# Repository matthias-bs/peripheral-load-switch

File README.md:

# peripheral-load-switch

Compact SMD peripheral load switch based on the Vishay SiP32431, designed for enabling/disabling power to microcontroller peripherals.

## Description

A minimal, all-SMD load switch board for switching a peripheral's supply voltage under microcontroller control. The design uses the Vishay **SiP32431DR3** high-side switch in a SC-70-6 (SOT-363) package. Board-edge castellated contacts (J2, half-hole, DNP) allow direct PCB-to-PCB soldering or surface mounting. An optional 5-pin 2.54 mm pitch pin header (J1) provides access for prototyping with breadboards or Dupont wires.

## SiP32431 Key Specifications

Datasheet: [SiP32431 (Vishay, PDF)](https://www.vishay.com/docs/66597/sip32431.pdf)

| Parameter               | Value                              |
|-------------------------|------------------------------------|
| Operating voltage       | 1.5 V – 5.5 V                      |
| Max continuous current  | 1.2 A                              |
| R<sub>DS(on)</sub>      | 147 mΩ                             |
| Package                 | SC-70-6 (JEITA) / SOT-363 (JEDEC)  |
| Enable logic            | Active-high                        |
| Switch type             | High-side                          |
| Leakage current         | 10 pA (ultra-low)                  |
| Special features        | Reverse current blocking, soft-start, ultra-low quiescent current |

## PCB & Schematic Features

- All-SMD design; 0805 passives are (more or less) hand-solderable, SC-70-6 IC requires reflow soldering
- 1 MΩ pull-down on EN pin ensures switch-off when enable is floating
- 1 µF input and 100 nF output decoupling capacitors
- 5-pin 2.54 mm pitch half-hole edge connector (J2, DNP) — castellated board-edge contacts for PCB-to-PCB or surface mounting
- 5-pin 2.54 mm pitch pin header (J1, optional) — for PCB-to-PCB stacking or prototyping with breadboards or Dupont wires
- DRC-clean design (0 violations, 0 unconnected pads)
- KiCad 9 source files with custom `Edge_HalfHole_5Pin_2.54mm` footprint included

## Schematic Preview

*Click image to open interactive schematic viewer (KiCanvas)*

## Interactive 3D PCB View

*Click image to open the interactive 3D model viewer (rotate/zoom/pan) — or use [KiCanvas](https://kicanvas.org/?github=https%3A%2F%2Fgithub.com%2Fmatthias-bs%2Fperipheral-load-switch%2Fblob%2Fmain%2Fload_switch.kicad_pcb) for a full PCB layer inspector*

> **How it was generated:** The 3D model ([`docs/load_switch.glb`](docs/load_switch.glb)) was exported from KiCad 9 using `kicad-cli pcb export glb` with tracks, pads, zones, silkscreen and soldermask included. The viewer ([`docs/index.html`](docs/index.html)) is a custom [Three.js](https://threejs.org/) page served via GitHub Pages.

## Bill of Materials

| Ref      | Value       | Footprint        | Description                        | LCSC Part # |
|----------|-------------|------------------|------------------------------------|-------------|
| U1       | SiP32431DR3 | SC-70-6 (SOT-363)| High-side load switch              | [C141606](https://www.lcsc.com/product-detail/C141606.html) |
| R1       | 1 MΩ        | 0805             | Pull-down on EN pin                | [C17514](https://www.lcsc.com/product-detail/C17514.html)  |
| C_IN1    | 1 µF        | 0805             | Input decoupling capacitor         | [C1712](https://www.lcsc.com/product-detail/C1712.html)   |
| C_OUT1   | 100 nF      | 0805             | Output decoupling capacitor        | [C126469](https://www.lcsc.com/product-detail/C126469.html) |
| J1       | —           | PinSocket 1×5 2.54 mm     | Optional pin header | — |
| J2       | —           | Half-hole 5-pin 2.54 mm (DNP¹) | Edge connector | — |

> ¹ DNP = Do Not Populate — the half-hole edge connector (J2) is a PCB manufacturing feature: the through-holes are routed in half at the board edge to form castellated contacts. No separate component is soldered.
>
> LCSC Part # are ordering references for [lcsc.com](https://lcsc.com).

## Connector Pinout (J2 — half-hole edge connector)

| Pin | Signal | Description          |
|-----|--------|----------------------|
| 1   | GND    | Ground               |
| 2   | GND    | Ground               |
| 3   | EN     | Enable (active-high) |
| 4   | OUT    | Switched output      |
| 5   | IN     | Supply voltage input |

## Production Files

Ready-to-order Gerber files (standard RS-274X, compatible with any PCB fab) are in the [`production/`](production/) folder.

## License

Copyright 2026 Matthias Prinke

`SPDX-License-Identifier: Apache-2.0 WITH SHL-2.1`

Licensed under the [Solderpad Hardware License v2.1](https://solderpad.org/licenses/SHL-2.1/). See [LICENSE](LICENSE) for the full text.

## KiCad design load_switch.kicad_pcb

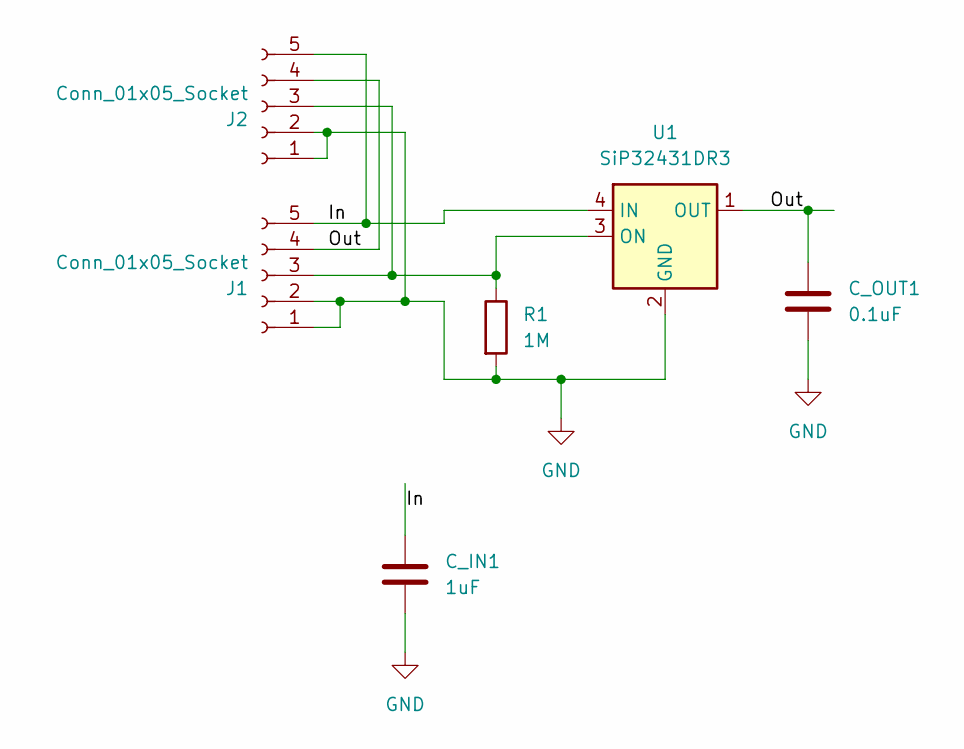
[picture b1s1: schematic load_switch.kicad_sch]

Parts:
C_IN1: 1uF; C_0805_2012Metric
C_OUT1: 0.1uF; C_0805_2012Metric
J1: Conn_01x05_Socket; PinSocket_1x05_P2.54mm_Vertical
J2: Conn_01x05_Socket; Edge_HalfHole_5Pin_2.54mm
R1: 1M; R_0805_2012Metric
U1: SiP32431DR3; SOT-363_SC-70-6

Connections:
/In: C_IN1.1, J1.5, J2.5, U1.4 (IN)
/Out: C_OUT1.1, J1.4, J2.4, U1.1 (OUT)
GND: C_IN1.2, C_OUT1.2, J1.1, J1.2, J2.1, J2.2, R1.2, U1.2 (GND), U1.5 (GND)
unnamed: J1.3, J2.3, R1.1, U1.3 (ON)

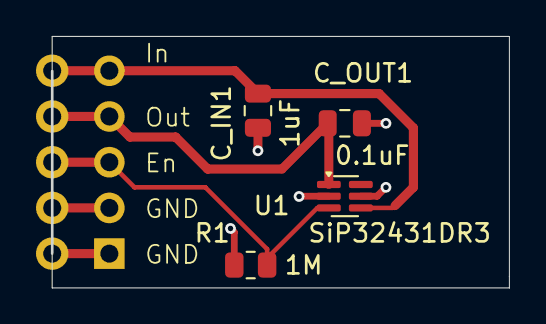
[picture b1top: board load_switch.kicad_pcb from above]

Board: 2 copper layers, 25.4 x 14.0 mm, 6 parts (1 on the bottom side), 4 nets.

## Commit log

2026-05-08 Initial release: SiP32431-based load switch, v0.1.0
2026-05-08 Fix connector pinout and hand-solderable remark in README
2026-05-08 BOM: clarify LCSC Part # column with links and explanatory note
2026-05-08 Add 3D render of PCB and embed as clickable KiCanvas link in README
2026-05-08 Add GLB 3D model for interactive GitHub viewer; update README link
2026-05-08 Add GitHub Pages 3D viewer (Three.js/GLB); explain DNP acronym; update README link
2026-05-08 Fix initial 3D view: correct camera for Z-up KiCad GLB orientation
2026-05-08 Fix J1/J2 swap in BOM; correct DNP footnote for half-hole edge connector
2026-05-08 Fix silkscreen Z-fighting: enable logarithmic depth buffer
2026-05-08 Fix Z-fighting: apply polygon offset per PCB layer (silk/mask/copper)
2026-05-08 Add SiP32431 datasheet link
2026-05-08 Add note on 3D PCB view generation method
2026-05-08 Clarify hand-solderability of 0805 passives in README.md
2026-05-08 Fix connector descriptions: clarify J1 (optional pin header) and J2 (DNP castellated contacts)
2026-05-08 Update J1 description: clarify usage for PCB-to-PCB stacking and prototyping
2026-05-08 Refine J1 and J2 descriptions in README.md for clarity

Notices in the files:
README.md:
License: SHL-2.1
load_switch.kicad_pcb:
©2026 M.Prinke SHL-2.1
